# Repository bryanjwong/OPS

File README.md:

# OPS
IEEE Open Project Space 2018-2019, educational projects teaching fundamental EE skills

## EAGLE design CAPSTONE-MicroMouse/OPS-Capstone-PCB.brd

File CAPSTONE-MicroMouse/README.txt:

This project is the culmination of the OPS program. Design, code, and build an autonomous robot that can navigate a newly 
encountered maze.

Features:
- Powered by an Arduino NANO
- Uses 3 IR Emitter/Receiver Sensors and PID control system to correct against wall collision
- Custom-designed PCB using Autodesk Eagle software
- IR Sensor-aided turns
- Plays celebratory music upon maze completion :)

Notes:
- Achieved the fastest time of any team at the OPS Capstone Competition

Video Demo here: https://youtu.be/ILv4s27H3WU

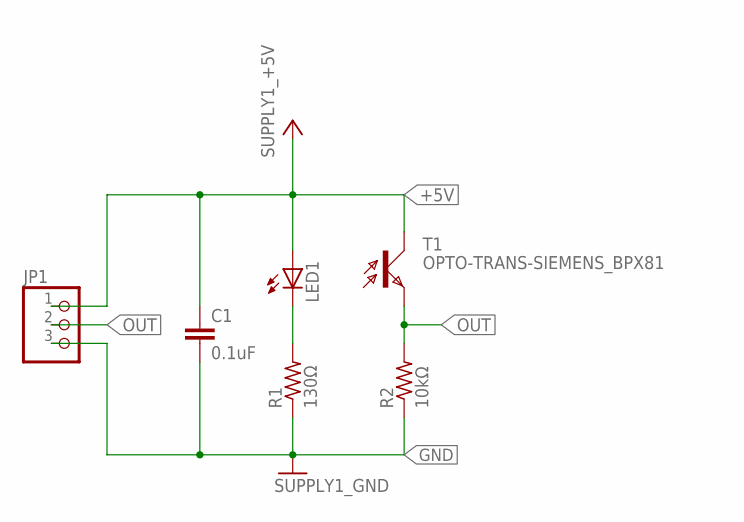
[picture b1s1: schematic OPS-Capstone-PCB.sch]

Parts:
C1: 0.1uF; RCL_C1206
JP1: PINHEAD_PINHD-1X3; PINHEAD_1X03
LED1: LED_LED5MM
R1: 130Ω; RCL_R1206
R2: 10kΩ; RCL_R1206
T1: OPTO-TRANS-SIEMENS_BPX81

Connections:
+5V: C1.1, JP1.1, LED1.A, T1.C
GND: C1.2, JP1.3, R1.1, R2.1
unnamed: LED1.K (C), R1.2
OUT: JP1.2, R2.2, T1.E

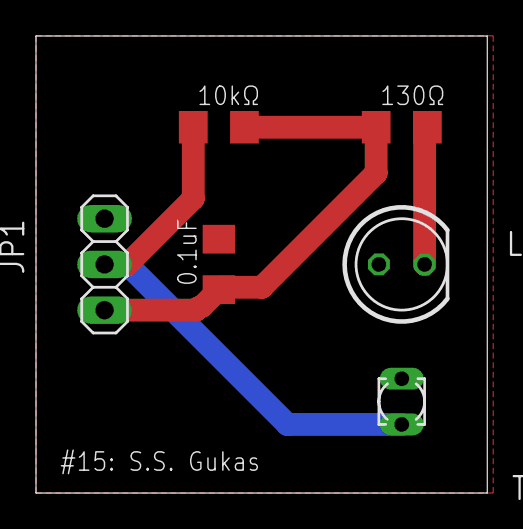
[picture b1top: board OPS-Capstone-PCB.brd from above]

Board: 2 copper layers, 25.1 x 25.4 mm, 6 parts (0 on the bottom side), 4 nets.

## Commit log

2019-03-10 Create CAPSTONE-MicroMouse
